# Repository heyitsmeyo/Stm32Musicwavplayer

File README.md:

This project is about making a music wav player with stm32f407 microcontroller 
the player has many features like playing , stopping or resuming the audio you want to listen to also you can adjust the volume , mute it or repeat the audio to listen again to it and all that is displayed on a lcd scrren. 
the audio files are stored in a sd card which is connected to the stm32 board with an otg cable via a sd card reader. 
The protocols used in this project are I2S and I2C. 

To build this project , you need : 
a stm32 board that has the CS4321 chip integrated in. 
LCD display , some push buttons. 
SD card , otg cable and sd card reader , 
you also need to speakers (or you can use headphones that support jack port) .

# Schematic : 

# PCB Design : 

# if you like the project , you can donate us for more : 

    https://ko-fi.com/heyitsmeyo

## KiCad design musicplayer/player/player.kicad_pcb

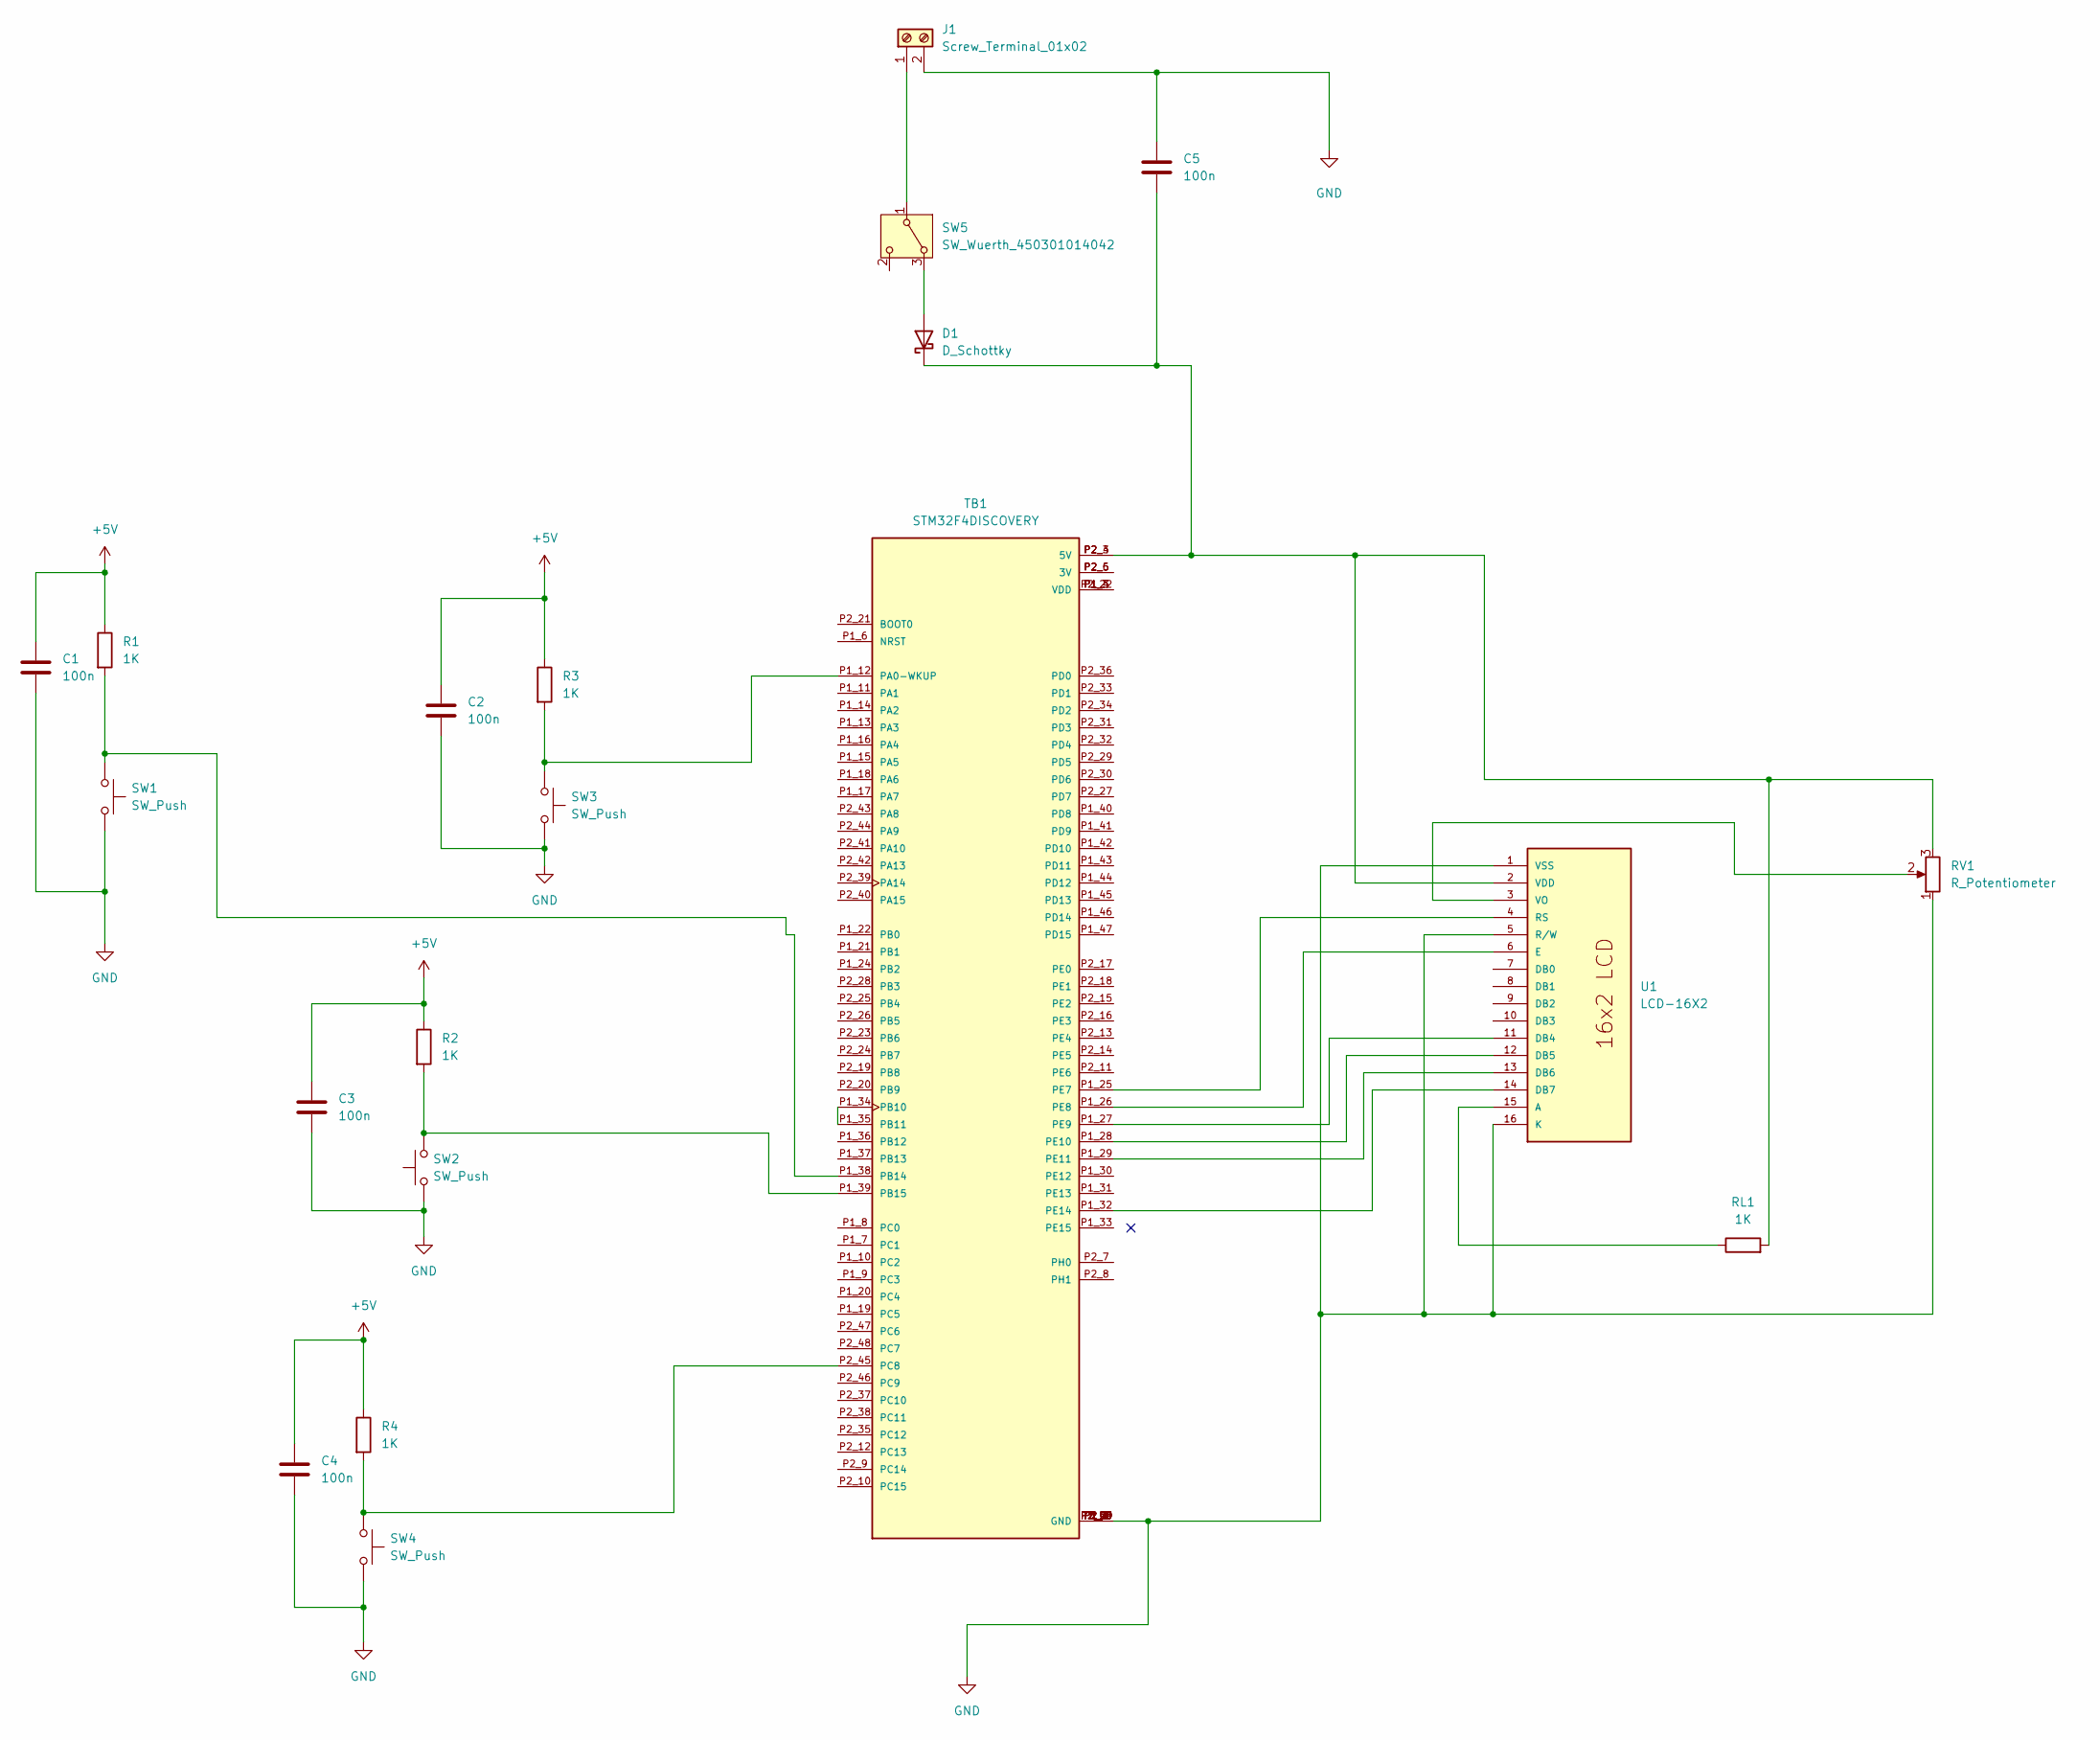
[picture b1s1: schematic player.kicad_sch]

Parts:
C1, C2, C3, C4, C5: 100n; CP_Axial_L10.0mm_D4.5mm_P15.00mm_Horizontal
D1: D_Schottky; D_DO-15_P10.16mm_Horizontal
J1: Screw_Terminal_01x02; screwterminal
R1, R2, R3, R4: 1K; R_Axial_DIN0309_L9.0mm_D3.2mm_P12.70mm_Horizontal
RL1: 1K; R_Axial_DIN0309_L9.0mm_D3.2mm_P12.70mm_Horizontal
RV1: R_Potentiometer; Potentiometer_ACP_CA6-H2,5_Horizontal
SW1, SW2, SW3, SW4: SW_Push; SW_PUSH_6mm_H4.3mm
SW5: SW_Wuerth_450301014042; SW_Slide-03_Wuerth-WS-SLTV_10x2.5x6.4_P2.54mm
TB1: STM32F4DISCOVERY; MODULE_STM32F4DISCOVERY; PARTREV 6
U1: LCD-16X2; MODULE_LCD-16X2; PARTREV N/A

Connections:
+5V: C1.1, C2.1, C3.1, C4.1, R1.1, R2.1, R3.1, R4.1
GND: C1.2, C2.2, C3.2, C4.2, C5.1, J1.2, RV1.1, SW1.2, SW2.1, SW3.2, SW4.2, TB1.P1_1 (GND), TB1.P1_2 (GND), TB1.P1_5 (GND), TB1.P1_23 (GND), TB1.P1_49 (GND), TB1.P1_50 (GND), TB1.P2_1 (GND), TB1.P2_2 (GND), TB1.P2_49 (GND), TB1.P2_50 (GND), U1.1 (VSS), U1.5 (R/W), U1.16 (K)
unnamed: D1.2 (A), SW5.3 (A)
unnamed: C5.2, D1.1 (K), RL1.2, RV1.3, TB1.P2_3 (5V), TB1.P2_4 (5V), U1.2 (VDD)
unnamed: J1.1, SW5.1 (B)
unnamed: TB1.P2_5 (3V), TB1.P2_6 (3V)
unnamed: R3.2, SW3.1, TB1.P1_12 (PA0-WKUP)
unnamed: TB1.P1_34 (PB10), TB1.P1_35 (PB11)
unnamed: R1.2, SW1.1, TB1.P1_38 (PB14)
unnamed: R2.2, SW2.2, TB1.P1_39 (PB15)
unnamed: R4.2, SW4.1, TB1.P2_45 (PC8)
unnamed: TB1.P1_25 (PE7), U1.4 (RS)
unnamed: TB1.P1_26 (PE8), U1.6 (E)
unnamed: TB1.P1_27 (PE9), U1.11 (DB4)
unnamed: TB1.P1_28 (PE10), U1.12 (DB5)
unnamed: TB1.P1_29 (PE11), U1.13 (DB6)
unnamed: TB1.P1_32 (PE14), U1.14 (DB7)
unnamed: TB1.P1_3 (VDD), TB1.P1_4 (VDD), TB1.P2_22 (VDD)
unnamed: RL1.1, U1.15 (A)
unnamed: RV1.2, U1.3 (VO)

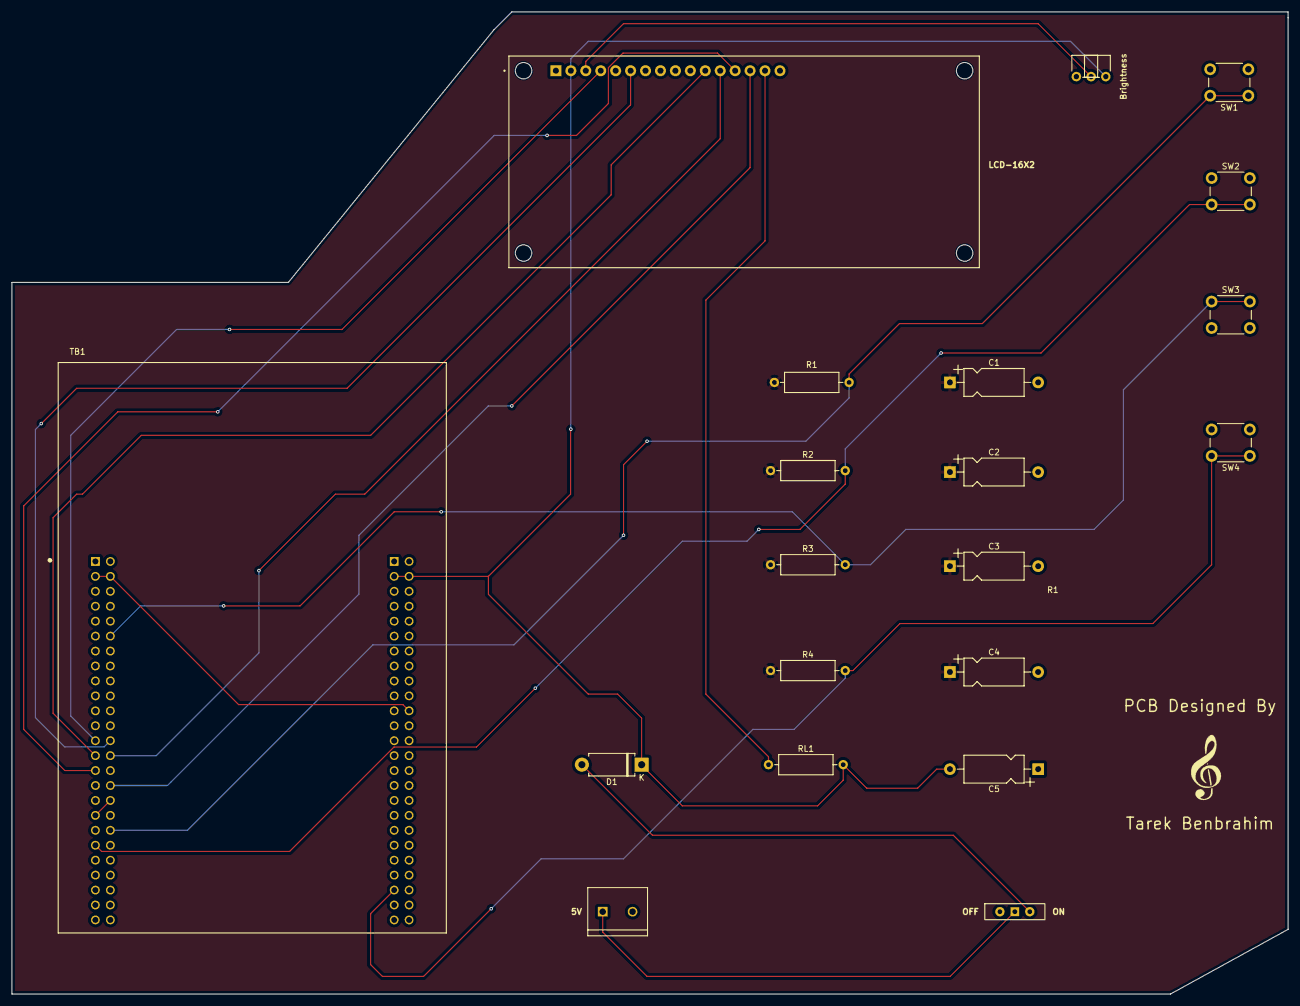
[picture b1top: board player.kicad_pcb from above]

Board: 2 copper layers, 217.0 x 167.0 mm, 20 parts (0 on the bottom side), 20 nets.
